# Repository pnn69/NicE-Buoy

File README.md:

# NicE-Buoy Autonomous Marine System Firmware

Welcome to the master repository for the **NicE-Buoy Autonomous Marine System**. This codebase powers a highly reliable, dual-processor autonomous marine buoy designed for GPS lock-to-position, remote configuration, automated sailing, and live telemetry tracking over LoRa and WiFi (UDP).

---

## 📌 Project Overview

NicE-Buoy is an industrial-grade marine robotic system consisting of multiple hardware and software components. Each buoy uses a **dual-ESP32 architecture** split into a **Top Unit (RoboTop)** and a **Sub Unit (RoboSub)**, connected by a single-wire half-duplex serial link. This physical decoupling isolates high-frequency navigation, radio communication, and web server tasks (Top) from raw thruster driving, compass polling, and the PID motor loops (Sub).

Alongside the buoys sit two shore-side controllers: **RoboCYD**, a touchscreen unit that doubles as the field WiFi access point, and **RoboLora**, a USB/WiFi LoRa gateway.

---

## 🏗️ System Architecture

```
        ┌───────────────────────────┐        ┌───────────────────────────────┐
        │  RoboPythonDisplay (PC)   │        │  RoboCYD (touchscreen)        │
        │  Tkinter dashboard        │        │  - IS the field AP Robo_WiFi  │
        └────────────┬──────────────┘        │  - LoRa RX task + web UI      │
                     │ UDP / LoRa            └───────────────┬───────────────┘
                     │                                       │
        ┌────────────▼──────────────┐                        │
        │  RoboLora (gateway)       │   UDP 1001 (protocol)  │
        │  USB + WiFi <-> LoRa      │   UDP 1002 (debug log) │
        └────────────┬──────────────┘                        │
                     └───────────────┬───────────────────────┘
                                     │  LoRa 868 MHz  +  WiFi/UDP
┌────────────────────────────────────▼────────────────────────────────────────┐
│                                  RoboTop                                    │
│  - GPS polling (TinyGPS++, 0,0 placeholder rejected)                        │
│  - LoraTask: RF telemetry, ACK retry table (10 slots)                       │
│  - WiFiTask: web dashboard, UDP broadcast, OTA, captive portal, mDNS        │
│  - SercomTask: bridge to the Sub          - Button, buzzer, RGB LEDs        │
└────────────────────────────────────┬────────────────────────────────────────┘
                                     │  single-wire half-duplex UART
                                     │  Top TX 22 / RX 21  <->  Sub RX 5 / TX 18
┌────────────────────────────────────▼────────────────────────────────────────┐
│                                  RoboSub                                    │
│  - Dual ESC thrusters (BB & SB)     - ICM-20948 9-DoF compass + fusion      │
│  - Rudder & speed PID loops         - Owns ALL tuning in NVS                │
│  - Its own web dashboard (24 endpoints) and OTA                            │
└─────────────────────────────────────────────────────────────────────────────┘
```

The codebase is structured into the following decoupled sub-projects:

1.  **`RoboTop` (Top Unit)** — ESP32, FreeRTOS. Acquires GPS, hosts the HTML5 control dashboard, broadcasts telemetry over UDP and LoRa, and delegates motor execution to the Sub.
    Tasks: `GpsTask`, `LoraTask`, `WiFiTask`, `SerialTask` (SercomTask), `buttonTask`, `LedTask`, `buzzTask`.
2.  **`RoboSub` (Sub Unit)** — ESP32, FreeRTOS. Drives the thrusters, reads the compass, runs the PID loops, and is the **authoritative owner of all tuning parameters** (see below).
    Tasks: `CompassTask`, `EscTask`, `SerialTask`, `WiFiTask`, `LedTask`, `buzzTask`. The rudder and speed PIDs live in `pidrudspeed.cpp`.
3.  **`RoboCYD` (Touchscreen Controller)** — ESP32 + 320x240 TFT with resistive touch. Displays the fleet, sends commands, and **raises the field access point `Robo_WiFi`** when no home network is present. Has a dedicated LoRa receive task and serves both a dashboard and a standalone fullscreen map.
4.  **`RoboDependency` (`RoboCompute` + `RoboTone` libraries)** — shared code linked by Top and Sub. Navigation maths (`RouteToPoint`), the unified `RoboStruct`, `formatFloat`, and the telemetry encoder/decoder (`rfCode` / `rfDeCode`).
5.  **`RoboLora` (LoRa Gateway)** — USB-and-WiFi to LoRa gateway with its own web UI. Relays operator commands to the buoys; stamps its outgoing frames with sender ID `0x99`.
6.  **`RoboPythonDisplay` (Python GUI Monitor)** — Tkinter desktop dashboard (`RoboControl.py`) for up to 3 buoys: windroses, thruster indicators, battery voltages, PID menus.
7.  **`RoboChargingStation`** — solar monitoring and charging dock firmware.

### Who owns what

Worth stating plainly, because it drives a lot of the design:

*   **The Sub owns the tuning.** PID gains, compass offset, `holdRad`, thruster inversion and swap all live in the Sub's NVS. The Top holds a RAM copy only, fetched via `SETUPDATA` when the serial link comes up, and shown on the dashboards until the Sub reports again.
*   **`compassOffset`, `revBB`, `revSB` and `swap_BB_SB` are hull-specific** — they describe the physical boat, not the electronics. Move a Sub to another hull and these travel with it and will be wrong until re-entered.
*   **The Sub has no LoRa.** Its only path to the outside world is the serial line to its Top.

---

## 🌐 Network Layout

Every node follows the same priority list:

```
NicE_WiFi  ->  Robo_WiFi  ->  its own AP
```

*   **At home** everything joins `NicE_WiFi`.
*   **In the field**, when no `NicE_WiFi` is in reach, the **CYD becomes `Robo_WiFi`** (password `geenanker`, `192.168.1.1/24`, 8 client slots) and the Tops and RoboLora join it.
*   **A node that finds neither** raises its own AP — `TOP_<id>`, `SUB_<id>`, `LORA_<id>`, password `geenanker`, on `192.168.4.1` — and keeps hunting underneath it. Joining that AP opens the dashboard automatically via a captive portal.
*   **The Sub deliberately skips `Robo_WiFi`**, to keep the CYD's client slots for the Tops and a phone. It costs nothing: the Sub never transmits on UDP anyway, and all of its telemetry reaches you folded into the Top's `TOPDATA`.

**mDNS** gives every node a stable name that works in both modes — `top-<id>.local`, `sub-<id>.local`, `robocyd.local`, `lora-<id>.local`. ArduinoOTA registers the responder; nothing else may call `MDNS.begin()`, as a second responder has crashed this hardware before.

**UDP ports:** `1001` carries the protocol; `1002` carries a plain-text debug log (see the RoboTop README).

---

## 📡 Communication Protocol & Frame Format

The system communicates using a lightweight, proprietary, ASCII-based comma-separated protocol designed to optimize RF bandwidth while remaining human-readable.

### Frame Anatomy
```
$TargetID,SenderID,AckType,CommandType,Status,Param1,Param2,...,ParamN*CRC\n
```

*   **`$`**: Starting sentinel character.
*   **`TargetID`**: Address of the recipient. **All IDs are hexadecimal.** A buoy's ID is the low four bytes of its MAC (e.g. `b7a5b578`). `1` (`BUOYIDALL`) is the broadcast address; `0` is treated as a legacy broadcast.
*   **`SenderID`**: Address of the transmitting station. `99` (i.e. `0x99`) is the web UI / RoboLora and `98` is the CYD display. **These two are the only senders whose broadcasts a buoy will act on** — a broadcast command from a peer buoy is ignored, which is what stops one buoy commanding another.
*   **`AckType`**: Packet type classification:
    *   `1 (GET)`: Request parameter values.
    *   `2 (SET)`: Modify parameter values.
    *   `3 (GETACK)`: Request command execution with receipt verification.
    *   `4 (ACK)`: Receipt confirmation.
    *   `6 (INF)`: Telemetry status update, or an *answer* to a question.
*   **`CommandType`**: Integer mapping to system command (e.g., `51` for `TOPDATA`, `19` for `BUOYPOS`, `83` for `SETUPDATA`, `47` for `DIRDIST`, `21` for `LOCKPOS`, `23` for `DOCKPOS`).
*   **`Status`**: Current state machine status of the buoy (`7 IDLE`, `13 LOCKED`, `16 DOCKED`, …).
*   **`Params`**: Dynamic floating-point or integer parameters depending on the command.
*   **`*`**: End-of-payload delimiter.
*   **`CRC`**: 2-character hexadecimal CRC calculated by XOR'ing all characters between `$` and `*`.

> **Broadcasts that expect an ACK are a trap.** An ACK for `IDr = BUOYIDALL` can never match in `removeAckMsg()`, so a `SET` or `GETACK` broadcast sits in the LoRa retry table for all five retransmits and blocks a slot. Broadcast beacons must use `INF`.

---

## 🚀 Advanced Telemetry Optimizations

### 1. Bandwidth Compression
To maximize LoRa airtime efficiency and range, telemetry strings undergo two compression steps in `RoboCompute.cpp`:
*   **Float Trailing Stripping**: `formatFloat()` trims redundant trailing zeros and decimal points (e.g. `12.5000` becomes `12.5`).
*   **Zero Compression**: `RoboCode()` compresses consecutive zero fields to empty strings (e.g. `,0,0,0,0,` becomes `,,,,,`).

### 2. The Top-to-Sub Link, and Why One-Way Failures Matter
The Top and Sub share **one wire**, half duplex, with hardware separating the two directions (opto-isolated; see `Datasheets/`). The firmware configures two GPIOs per board — Top TX 22 / RX 21, Sub RX 5 / TX 18 — but that is **not** two conductors.

*   **The diagnostic consequence:** if the connector or the wire fails, traffic stops in *both* directions. A failure in **one direction only** therefore cannot be the plug — it is in the direction-separation circuitry, which is per board. Swapping a Sub between hulls localises such a fault to a specific board.
*   `SercomTask` implements **echo filtering**, discarding frames whose sender ID is its own, because a transmitter hears itself on a shared wire.
*   **Implicit ACKs**: any valid `INF` response from the Sub signals that it processed the command, clearing the retry queue without extra traffic.
*   **The Sub sleeps.** After reconnection it sits in power-down and only wakes on an incoming command — send one, wait, then it communicates. Do not read a quiet Sub as a fault until it has been nudged.

### 3. Hardware Self-Healing Watchdogs
*   **LoRa transceiver watchdog**: if transmission fails for 500 ms the SPI/state machine is assumed locked and `InitLora()` forces a full re-init.
*   **Compass watchdog**: static I2C readings under thruster power trigger `COMPASS STUCK - REINIT`.
*   **Serial watchdog**: the Top clears `isSerConnected` after 2 s of silence and re-requests `SETUPDATA` when the Sub returns.
*   **Stack headroom is observable.** The Top's `/data` reports `StkLoop`, `StkLora`, `StkWifi`, `StkSer` and heap figures. A LoRa task running on 100 bytes of stack was the cause of a hard-to-find panic; check these after any change that adds work to a task.

---

## 🧭 In-Field Navigation Calibration State Machines

1.  **In-Field Compass Spin Calibration** — self-guided rotation while measuring magnetic min/max to derive hard-iron offsets.
2.  **In-Field Offset Alignment** — sails a straight leg on compass heading, compares the GPS track, and writes the difference to the stored compass offset.
3.  **Guided 8-Point Compass Calibration** — the hull is turned to the compass's own zero and then indexed round a mechanical fixture 45° at a time, one capture per mark. Produces the 8-point correction table, which is held on the Sub and reported through `SETUPDATA`. The table describes the hull's magnetic deviation only; which way the sensor is bolted in is a separate setting (**Set as North**), applied after the table.

    A GPS-based version of this used to exist, sailing eight 100 m legs and inferring the table from the track. It was removed when the mounting offset moved out of the table's input — its residual arithmetic assumed the old ordering.

---

## 🛠️ Developer Guide

### Prerequisites
*   **Firmware**: [VS Code](https://code.visualstudio.com/) + [PlatformIO IDE](https://platformio.org/).
*   **Python Monitor**: Python 3.10+ with `pyserial` and `tkinter`.

### Compilation & Flash Commands
```bash
pio run                      # build
pio run -t upload            # upload (OTA by default for Top and Sub)
pio device monitor           # serial monitor
```

### Over-The-Air (OTA) Updates
`RoboTop` and `RoboSub` default to `upload_protocol = espota`, so a plain upload goes over the network:

```bash
pio run -t upload --upload-port 192.168.1.71        # by address
pio run -t upload --upload-port top-b7a5099c.local  # or by mDNS name
```

`RoboCYD` and `RoboLora` have **no espota configuration** in their `platformio.ini` (their `upload_port` names a COM port that may not exist), so flash those directly:

```bash
python ~/.platformio/packages/framework-arduinoespressif32/tools/espota.py \
       -i <ip> -p 3232 -f .pio/build/<env>/firmware.bin -r
```

A RoboTop change that touches `data/` also needs `pio run -t uploadfs` — the web page lives in SPIFFS.

> Renaming an SSID or changing the WiFi policy must be rolled out to **the whole fleet at home on `NicE_WiFi`**. A device left on the old scheme cannot be reached in the field.

### Running the Python GUI Dashboard
```bash
pip install pyserial
python RoboPythonDisplay/RoboControl.py
```

---

## 📜 License & Contributions
This project is proprietary and confidential. For contributions, pull requests, or feature requests, contact **Peter de Nijs** (`pnn69pnn@gmail.com`).

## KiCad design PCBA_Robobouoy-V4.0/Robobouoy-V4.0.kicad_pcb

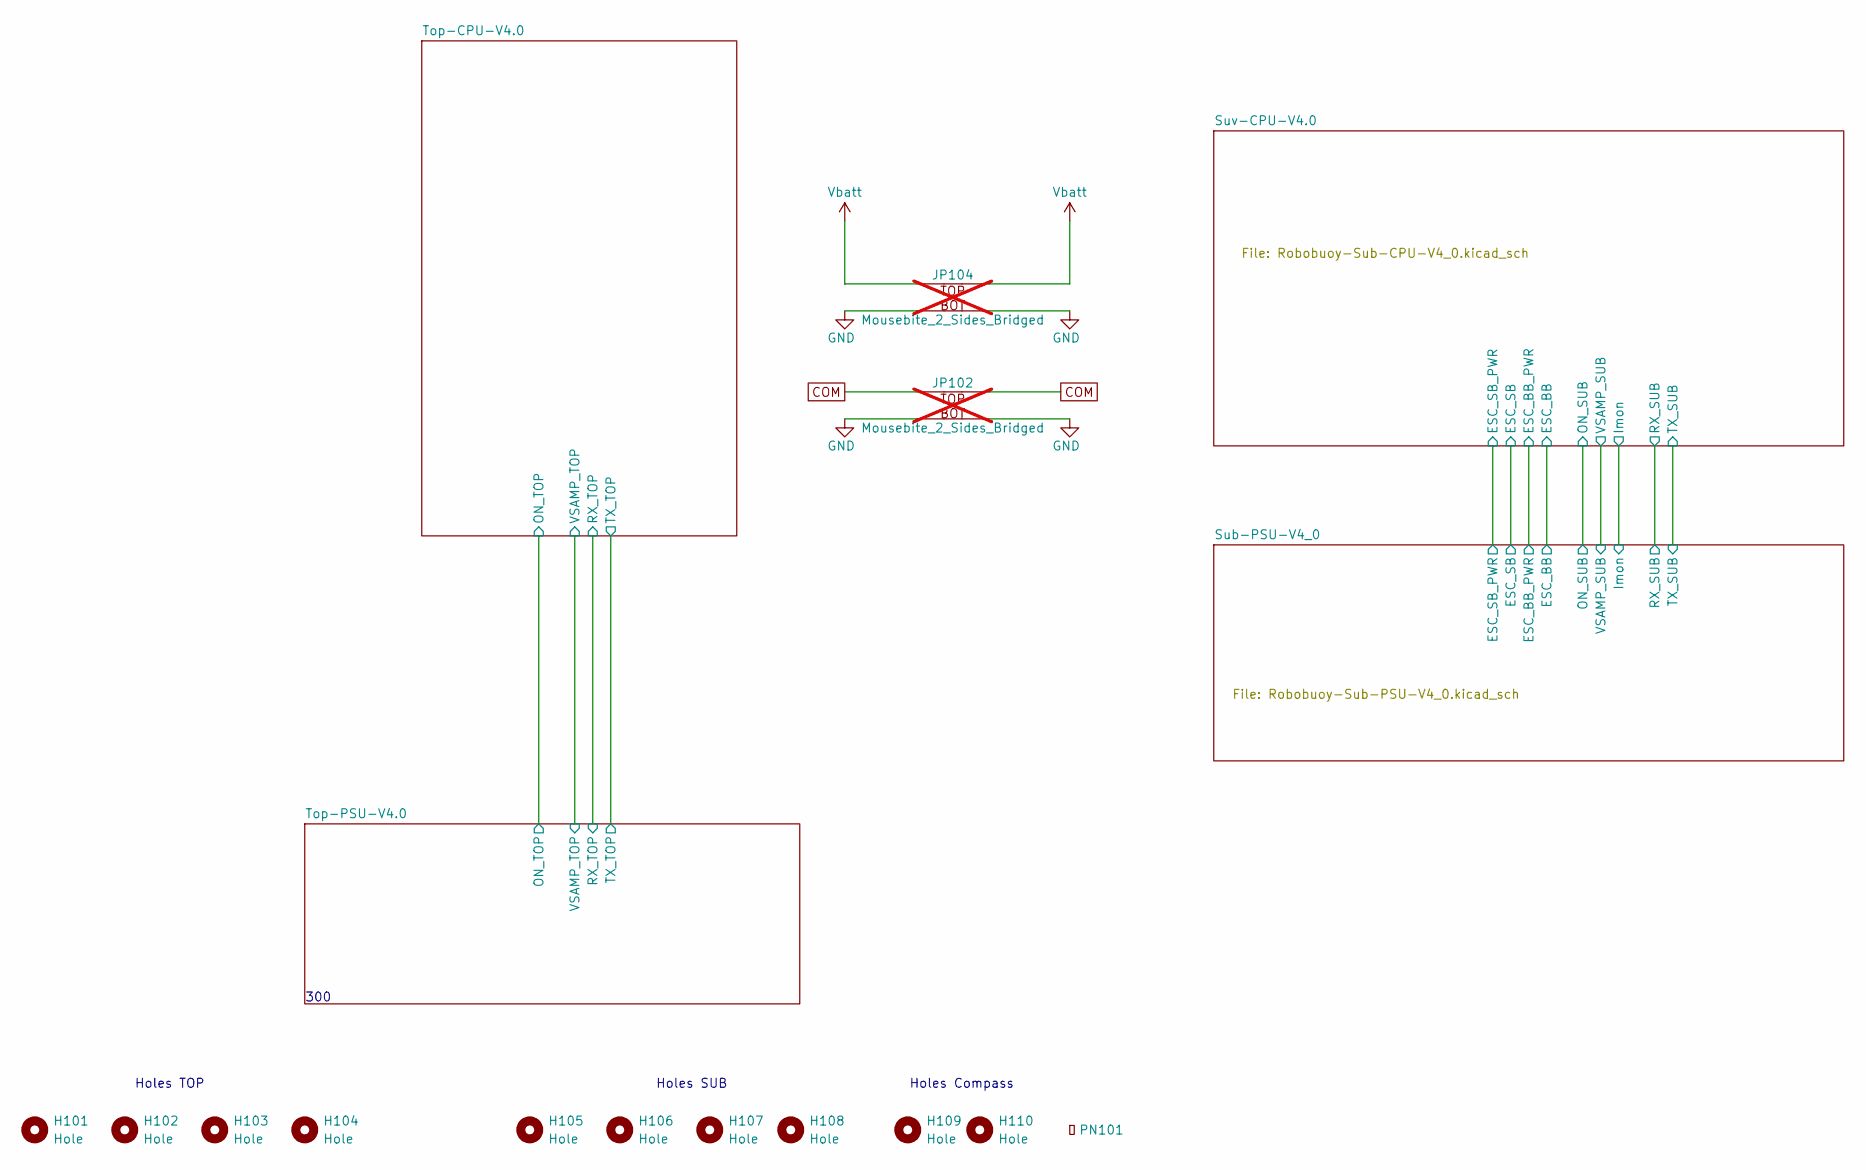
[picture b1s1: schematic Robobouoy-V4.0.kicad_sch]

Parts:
H101, H102, H103, H104, H105, H106, H107, H108, H109, H110: Hole; Hole_3.1mm
JP102, JP104: Mousebite_2_Sides_Bridged; MousebitConnectorDoubleSided; not fitted
PN101: Part_Num_JLCPCB

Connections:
COM: JP102.1 (A), JP102.2 (B); also elsewhere on the board
GND: JP102.3 (C), JP102.4 (D), JP104.3 (C), JP104.4 (D); also elsewhere on the board
Vbatt: JP104.1 (A), JP104.2 (B); also elsewhere on the board

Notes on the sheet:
Holes TOP
300
Holes SUB
Holes Compass

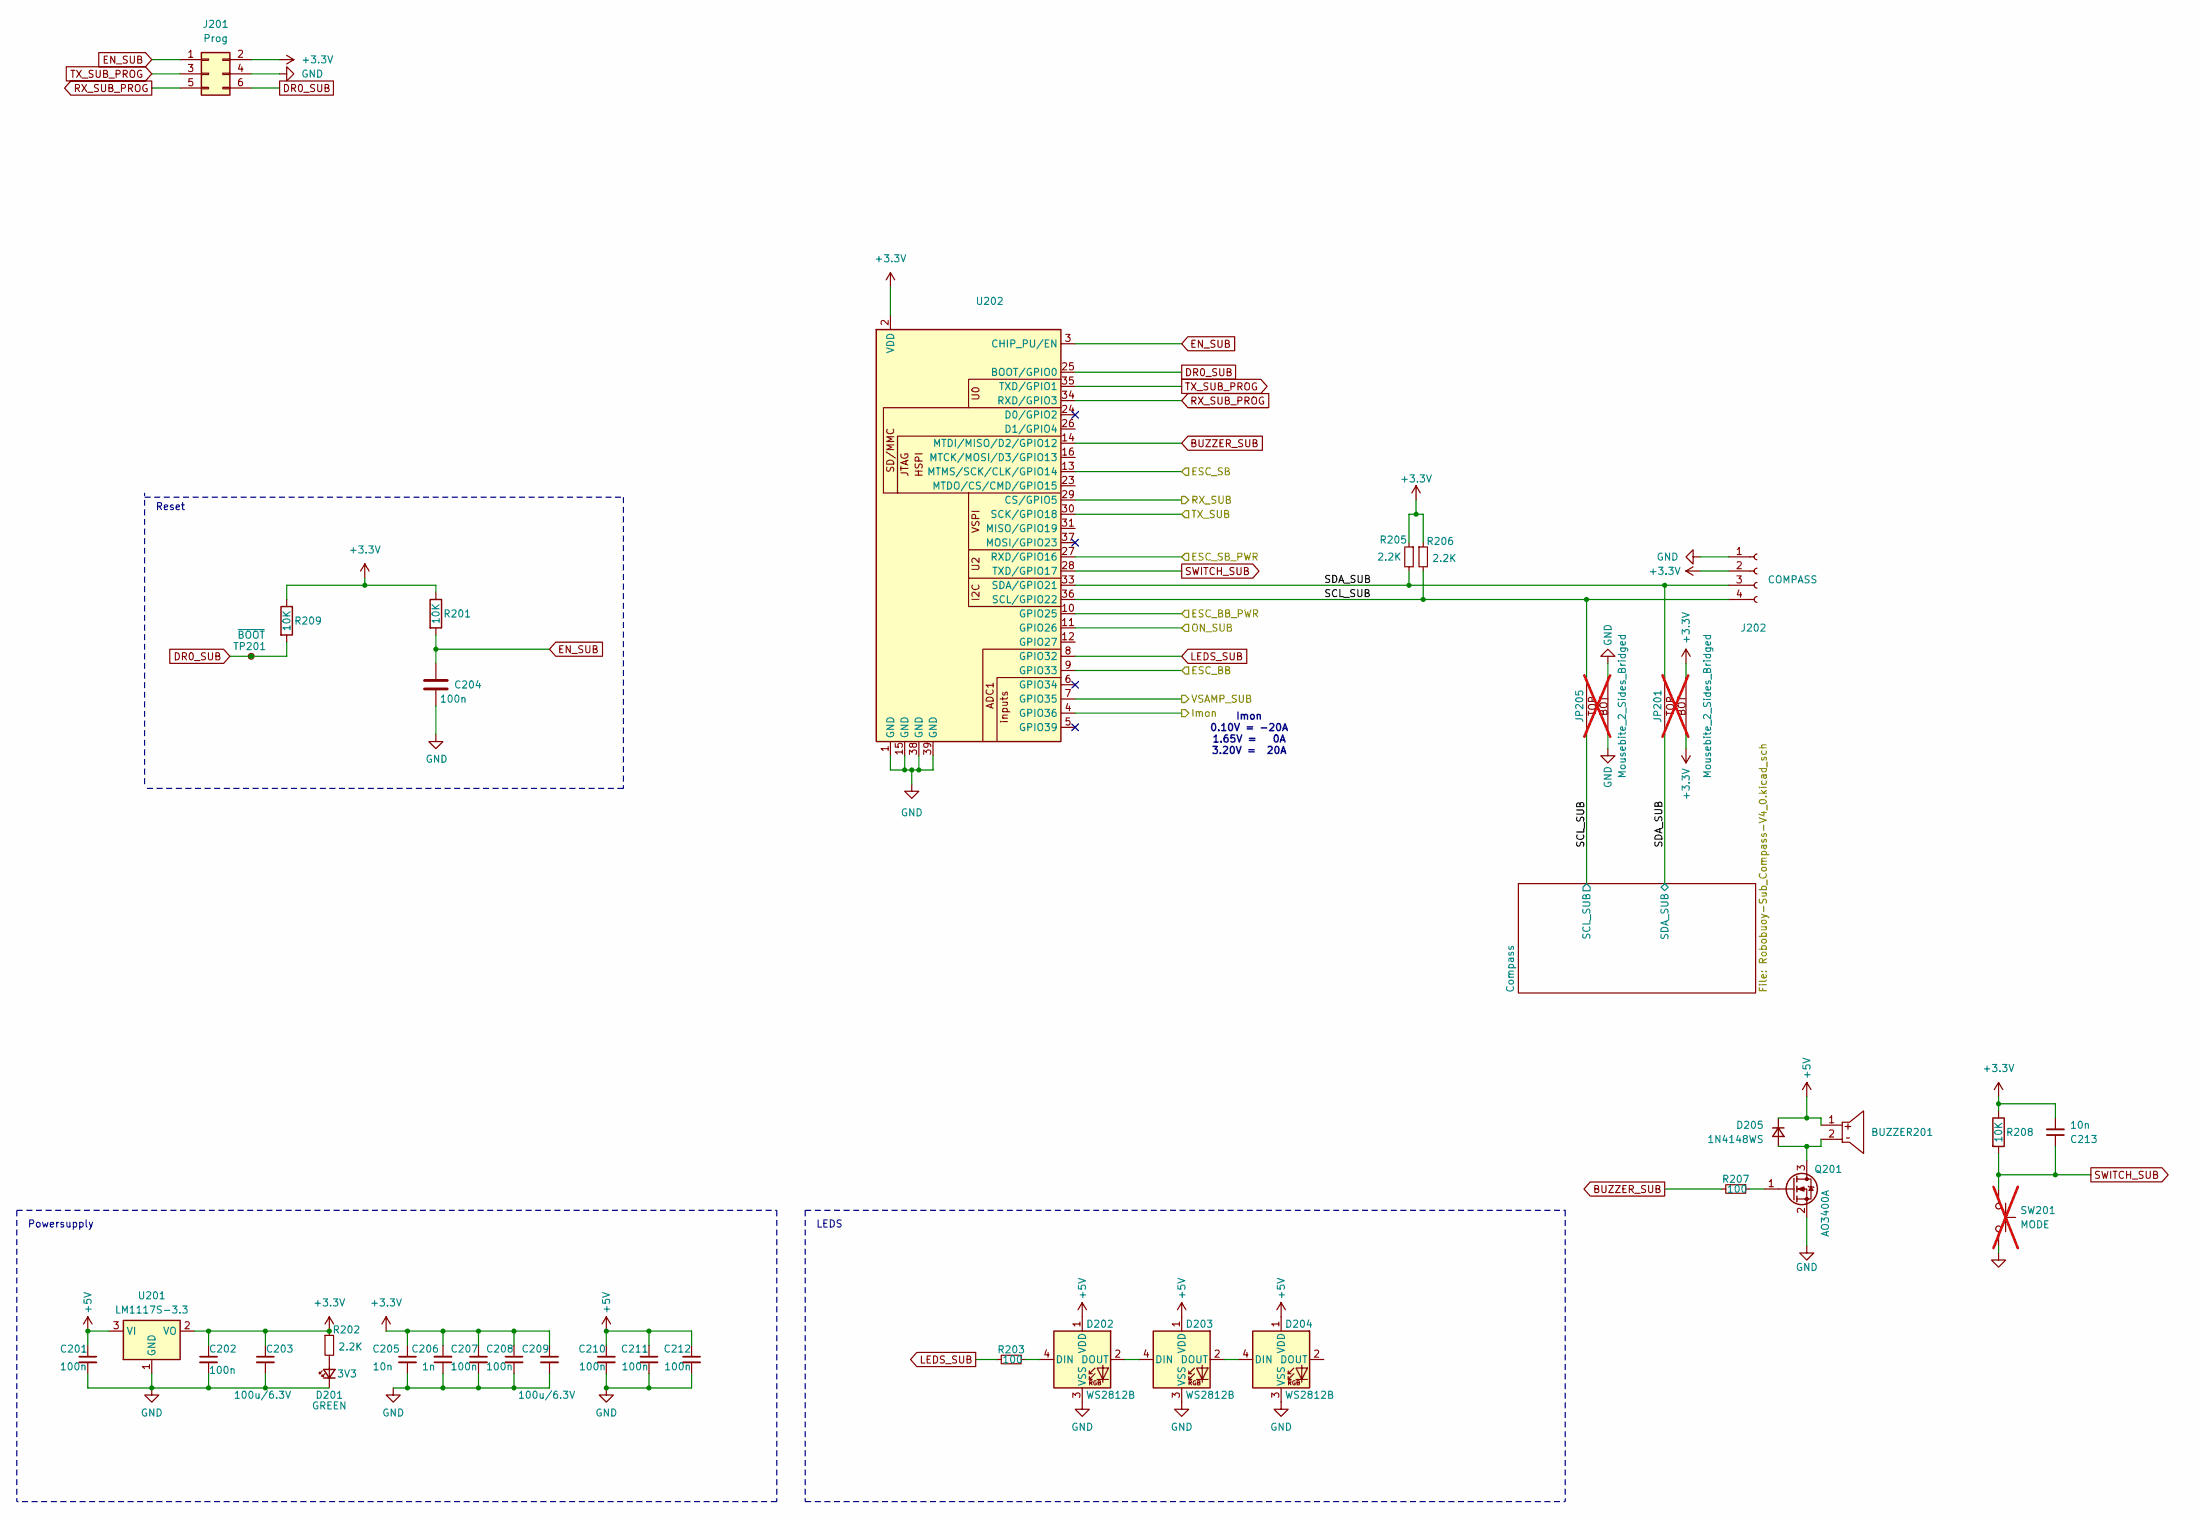
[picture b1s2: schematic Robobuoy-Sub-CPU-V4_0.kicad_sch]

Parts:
BUZZER201: CY-12085G-3016-P4; BUZ-TH_BD12.0-P6.50-D0.6-FD; MPN Cy-12085G-3016-P4; LCSC Part C968749
C201, C202, C204, C207, C208, C210, C211, C212: 100n; C_0603; LCSC C14663
C203, C209: 100u/6.3V; C_1206_3216Metric; LCSC C16133
C205, C213: 10n; C_0603; LCSC C57112
C206: 1n; C_0603; LCSC C1588
D201: GREEN; LED_0603_1608Metric; LCSC C12624
D202, D203, D204: WS2812B; LED_WS2812B_PLCC4_5.0x5.0mm_P3.2mm; LCSC C2843785
D205: 1N4148WS; D_SOD-323_1.8x1.4x1.15; LCSC C2128
J201: Prog; IDC_2x3_1.27mm; LCSC C42372545
J202: COMPASS; JST_XH_B4B-XH-A_1x04_P2.50mm_Vertical; LCSC C5341203
JP201, JP205: Mousebite_2_Sides_Bridged; MousebitConnectorDoubleSided; not fitted
Q201: AO3400A; SOT-23; LCSC C20917
R201, R208, R209: 10K; R_0603; Farnell 2331736
R202, R205, R206: 2.2K; R_0603; LCSC C4190
R203, R207: 100; R_0603; LCSC C22775
SW201: MODE; Header_1x02_P2.54_Jumper; not fitted
TP201: ~{BOOT}; Testpad_1
U201: LM1117S-3.3; SOT223; LCSC C6186
U202: ESP32-WROOM-32E_(visible_peripherals); ESP32-WROOM-32; LCSC C82899

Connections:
+3.3V: C202.1, C203.1, C205.1, C206.2, C207.1, C208.1, C209.1, C213.2, J201.2, J202.2, JP201.3 (C), JP201.4 (D), R201.1, R202.1, R205.1, R206.1, R208.1, R209.1, U201.2 (VO), U202.2 (VDD); also elsewhere on the board
+5V: BUZZER201.1, C201.1, C210.1, C211.1, C212.1, D202.1 (VDD), D203.1 (VDD), D204.1 (VDD), D205.1 (K), U201.3 (VI); also elsewhere on the board
/Sub-PSU-V4_0/ESC_BB: U202.9 (GPIO33); also elsewhere on the board
/Sub-PSU-V4_0/ESC_BB_PWR: U202.10 (GPIO25); also elsewhere on the board
/Sub-PSU-V4_0/ESC_SB: U202.13 (MTMS/SCK/CLK/GPIO14); also elsewhere on the board
/Sub-PSU-V4_0/ESC_SB_PWR: U202.27 (RXD/GPIO16); also elsewhere on the board
/Sub-PSU-V4_0/Imon: U202.4 (GPIO36); also elsewhere on the board
/Sub-PSU-V4_0/ON_SUB: U202.11 (GPIO26); also elsewhere on the board
/Sub-PSU-V4_0/RX_SUB: U202.29 (CS/GPIO5); also elsewhere on the board
/Sub-PSU-V4_0/TX_SUB: U202.30 (SCK/GPIO18); also elsewhere on the board
/Sub-PSU-V4_0/VSAMP_SUB: U202.7 (GPIO35); also elsewhere on the board
/Suv-CPU-V4.0/SCL_SUB: J202.4, JP205.1 (A), JP205.2 (B), R206.2, U202.36 (SCL/GPIO22); also elsewhere on the board
/Suv-CPU-V4.0/SDA_SUB: J202.3, JP201.1 (A), JP201.2 (B), R205.2, U202.33 (SDA/GPIO21); also elsewhere on the board
BUZZER_SUB: R207.2, U202.14 (MTDI/MISO/D2/GPIO12)
DR0_SUB: J201.6, R209.2, TP201.1 (1_1), U202.25 (BOOT/GPIO0)
EN_SUB: C204.1, J201.1, R201.2, U202.3 (CHIP_PU/EN)
GND: C201.2, C202.2, C203.2, C204.2, C205.2, C206.1, C207.2, C208.2, C209.2, C210.2, C211.2, C212.2, D201.1 (K), D202.3 (VSS), D203.3 (VSS), D204.3 (VSS), J201.4, J202.1, JP205.3 (C), JP205.4 (D), Q201.2 (S), SW201.1, U201.1 (GND), U202.1 (GND), U202.15 (GND), U202.38 (GND), U202.39 (GND); also elsewhere on the board
LEDS_SUB: R203.2, U202.8 (GPIO32)
unnamed: D201.2 (A), R202.2
unnamed: D202.4 (DIN), R203.1
unnamed: D202.2 (DOUT), D203.4 (DIN)
unnamed: D203.2 (DOUT), D204.4 (DIN)
unnamed: BUZZER201.2, D205.2 (A), Q201.3 (D)
unnamed: Q201.1 (G), R207.1
RX_SUB_PROG: J201.5, U202.34 (RXD/GPIO3)
SWITCH_SUB: C213.1, R208.2, SW201.2, U202.28 (TXD/GPIO17)
TX_SUB_PROG: J201.3, U202.35 (TXD/GPIO1)

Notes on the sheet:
LEDS
Imon 0.10V = -20A 1.65V = 0A 3.20V = 20A
Powersupply
Reset

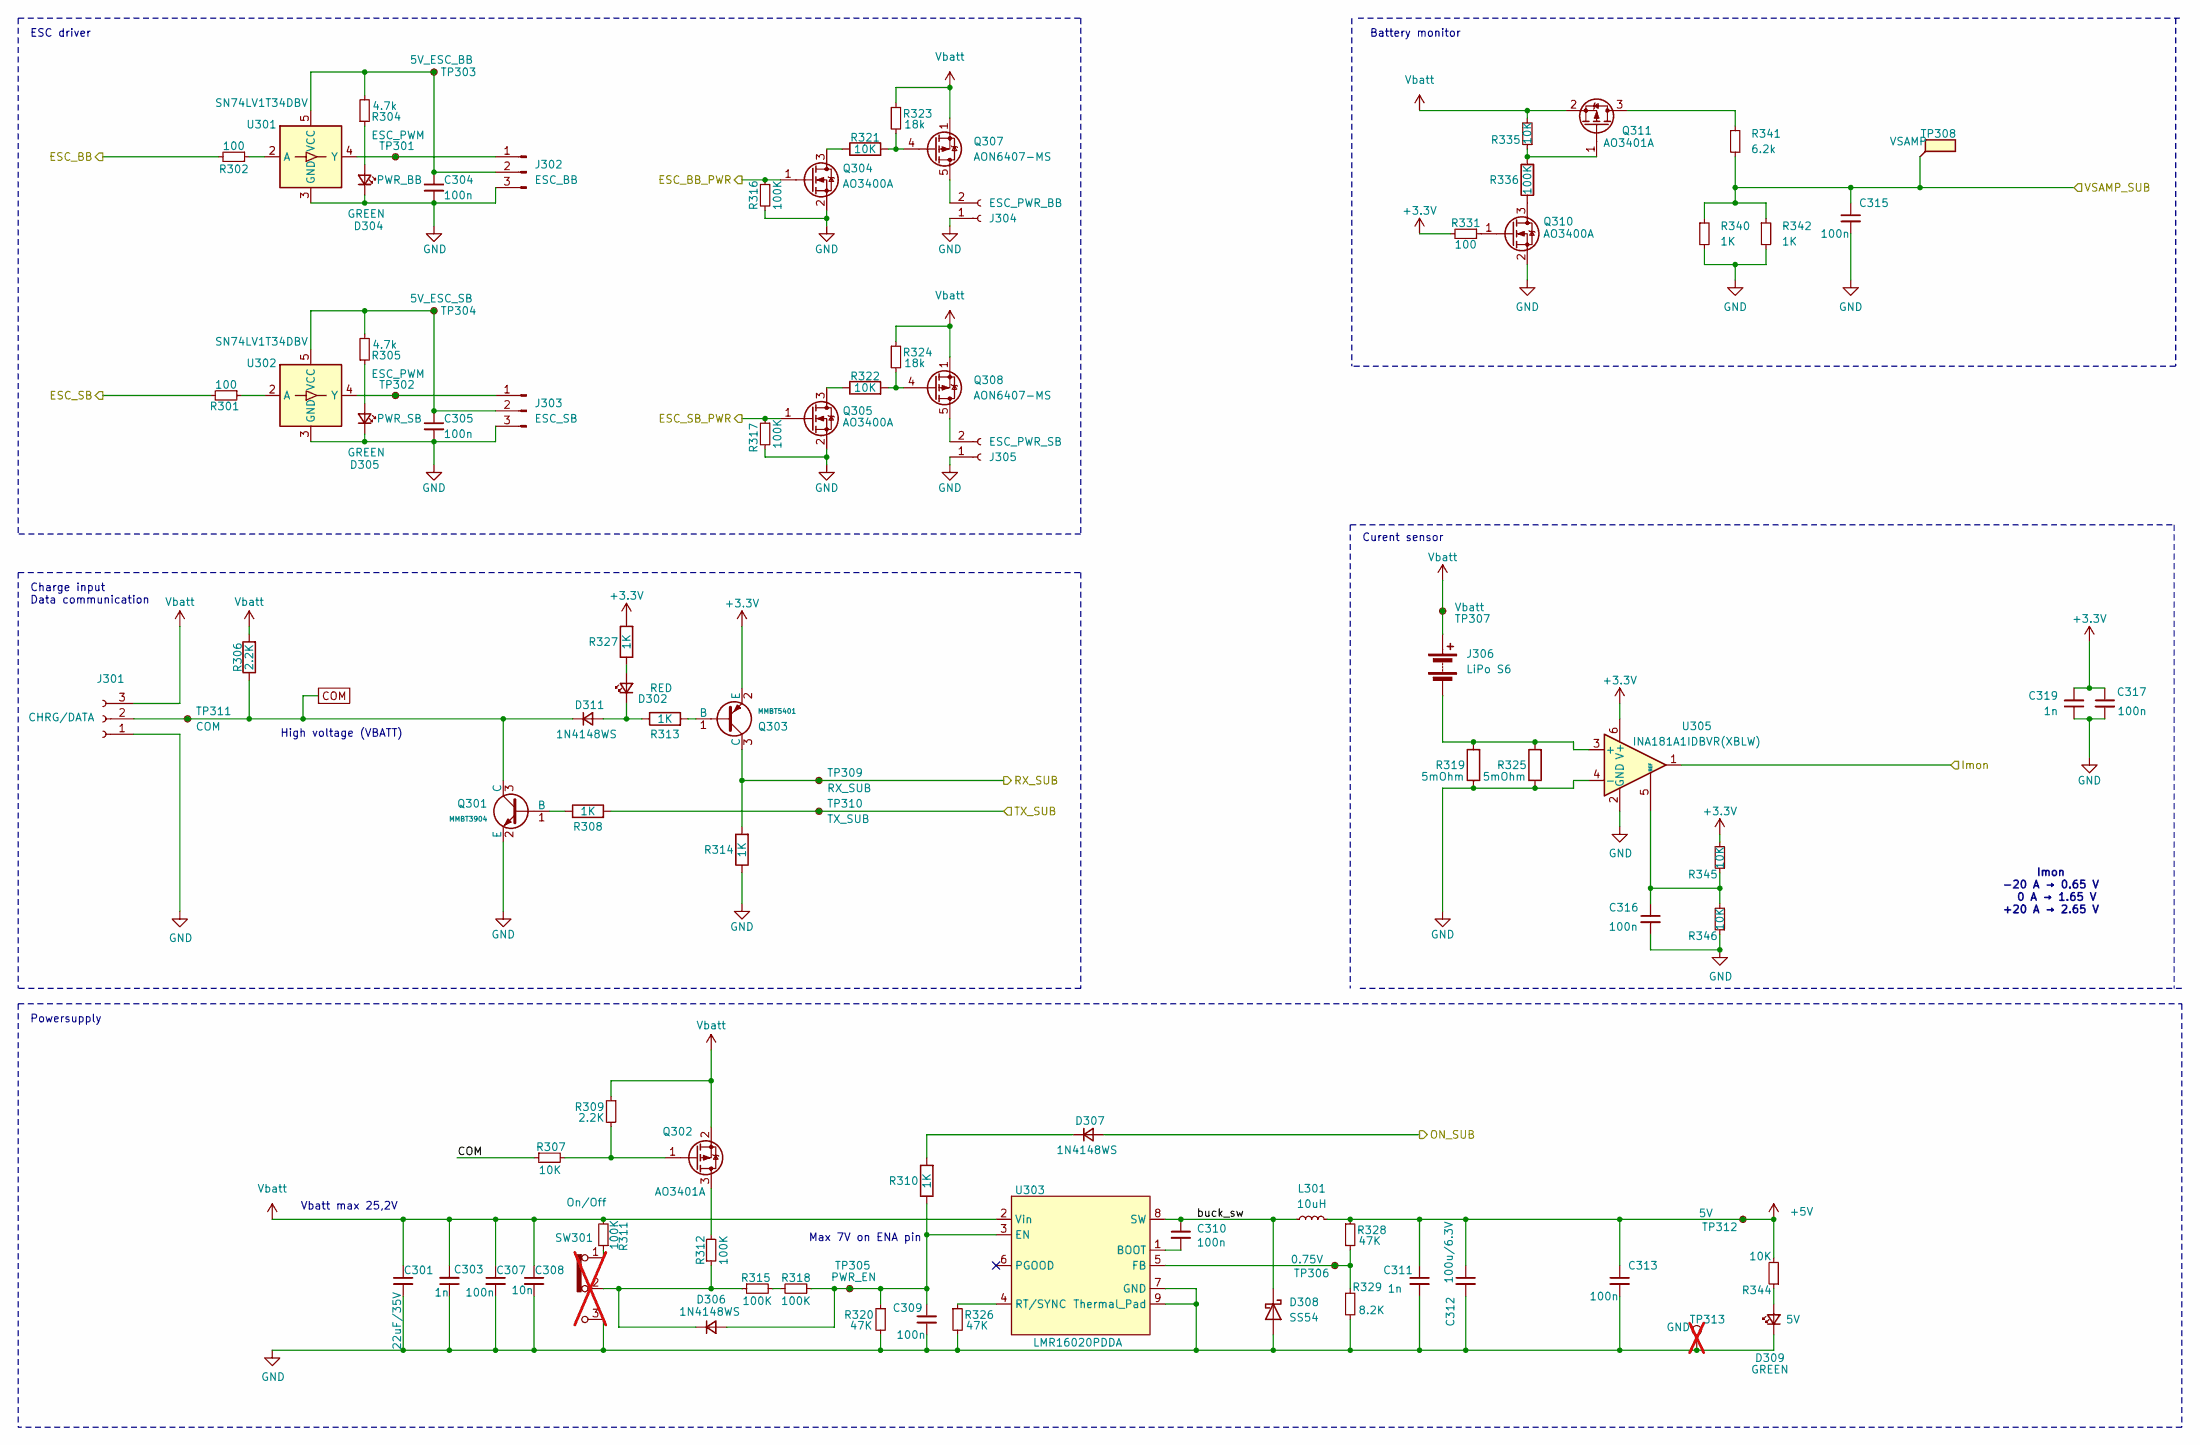
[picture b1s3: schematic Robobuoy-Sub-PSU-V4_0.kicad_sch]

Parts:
C301: 22uF/35V; C_1206_3216Metric; LCSC C6119969
C303, C311, C319: 1n; C_0603; LCSC C1588
C304, C305, C307, C309, C310, C313, C315, C316, C317: 100n; C_0603; LCSC C14663
C308: 10n; C_0603; LCSC C57112
C312: 100u/6.3V; C_1206_3216Metric; LCSC C16133
D302: RED; LED_0603_1608Metric; LCSC C2286
D304, D305, D309: GREEN; LED_0603_1608Metric; LCSC C2286
D306, D307, D311: 1N4148WS; D_SOD-323_1.8x1.4x1.15; LCSC C2128
D308: SS54; D_SMA; LCSC C22452
J301: CHRG/DATA; MR60PB-M; LCSC C53087234
J302: ESC_BB; JST_XH_B3B-XH-A_1x03_P2.50mm_Vertical; LCSC C5341202
J303: ESC_SB; JST_XH_B3B-XH-A_1x03_P2.50mm_Vertical; LCSC C5341202
J304: ESC_PWR_BB; AMASS_XT60PB-F_1x02_P7.20mm_Vertical; LCSC C19268038
J305: ESC_PWR_SB; AMASS_XT60PB-F_1x02_P7.20mm_Vertical; LCSC C19268038
J306: LiPo S6; AMASS_XT60PB-M_1x02_P7.20mm_Vertical; LCSC C19268037
L301: 10uH; L_6.6x7.0mm; LCSC C2894722
Q301: MMBT3904; Q_SOT-23; Part MMBT3904; LCSC C7420353
Q302, Q311: AO3401A; SOT-23; LCSC C15127
Q303: MMBT5401; Q_SOT-23; Part MMBT5401; LCSC C7420356
Q304, Q305, Q310: AO3400A; SOT-23; LCSC C20917
Q307, Q308: AON6407-MS; AO_DFN-8-1EP_5.55x5.2mm_P1.27mm_EP4.12x4.6mm; LCSC C17702953
R301, R302, R331: 100; R_0603; LCSC C22775
R304, R305: 4.7k; R_0603; LCSC C4177
R306, R309: 2.2K; R_0603; LCSC C4190
R307, R321, R322, R335, R344, R345, R346: 10K; R_0603; LCSC C25804
R308, R310, R313, R314, R327, R340, R342: 1K; R_0603; LCSC C21190
R311, R312, R315, R316, R317, R318, R336: 100K; R_0603; LCSC C25803
R319, R325: 5mOhm; R_1206; LCSC C7419996
R320, R326, R328: 47K; R_0603; LCSC C25819
R323, R324: 18k; R_0603; LCSC C25810
R329: 8.2K; R_0603; LCSC C25981
R341: 6.2k; R_0603; LCSC C4260
SW301: On/Off; Header_1x03_P2.54_Male; LCSC C2937625; not fitted
TP301, TP302: ESC_PWM; Testpad_1
TP303: 5V_ESC_BB; Testpad_1
TP304: 5V_ESC_SB; Testpad_1
TP305: PWR_EN; Testpad_1
TP306: 0.75V; Testpad_1
TP307: Vbatt; Testpad_1
TP308: VSAMP; Testpad_1
TP309: RX_SUB; Testpad_1
TP310: TX_SUB; Testpad_1
TP311: COM; Testpad_1
TP312: 5V; Testpad_1
TP313: GND; Testpoint_0.9x1.5; not fitted
U301, U302: SN74LV1T34DBV; SOT-23-5; LCSC C100024
U303: LMR16020PDDA; SOIC-8-1EP_3.9x4.9mm_P1.27mm_EP2.41x3.81mm_ThermalVias; LCSC C190006
U305: INA181A1IDBVR(XBLW); SOT-23-6; LCSC C45351496

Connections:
+3.3V: C317.1, C319.2, Q303.2 (E), R327.2, R331.2, R345.2, U305.6 (V+); also elsewhere on the board
+5V: C311.1, C312.1, C313.1, L301.2, R328.1, R344.2, TP312.1 (1_1); also elsewhere on the board
/Sub-PSU-V4_0/ESC_BB: R302.2; also elsewhere on the board
/Sub-PSU-V4_0/ESC_BB_PWR: Q304.1 (G), R316.1; also elsewhere on the board
/Sub-PSU-V4_0/ESC_SB: R301.2; also elsewhere on the board
/Sub-PSU-V4_0/ESC_SB_PWR: Q305.1 (G), R317.1; also elsewhere on the board
/Sub-PSU-V4_0/Imon: U305.1; also elsewhere on the board
/Sub-PSU-V4_0/ON_SUB: D307.2 (A); also elsewhere on the board
/Sub-PSU-V4_0/RX_SUB: Q303.3 (C), R314.2, TP309.1 (1_1); also elsewhere on the board
/Sub-PSU-V4_0/TX_SUB: R308.2, TP310.1 (1_1); also elsewhere on the board
/Sub-PSU-V4_0/VSAMP_SUB: C315.1, R340.1, R341.2, R342.1, TP308.1 (1_1); also elsewhere on the board
/Sub-PSU-V4_0/buck_sw: C310.1, D308.1 (K), L301.1, U303.8 (SW)
COM: D311.1 (K), J301.2, Q301.3 (C), R306.1, R307.1, TP311.1 (1_1); also elsewhere on the board
GND: C301.2, C303.1, C304.2, C305.2, C307.2, C308.2, C309.2, C311.2, C312.2, C313.2, C315.2, C316.2, C317.2, C319.1, D304.1 (K), D305.1 (K), D308.2 (A), D309.1 (K), J301.1, J302.3, J303.3, J304.1, J305.1, Q301.2 (E), Q304.2 (S), Q305.2 (S), Q310.2 (S), R314.1, R316.2, R317.2, R319.1, R320.2, R325.1, R326.2, R329.2, R340.2, R342.2, R346.1, SW301.3, TP313.1 (1_1), U301.3 (GND), U302.3 (GND), U303.7 (GND), U303.9 (Thermal_Pad), U305.2 (GND), U305.4 (-); also elsewhere on the board
unnamed: D302.2 (A), R327.1
unnamed: D302.1 (K), D311.2 (A), R313.1
unnamed: D304.2 (A), R304.1
unnamed: D305.2 (A), R305.1
unnamed: C309.1, D306.2 (A), R310.1, R318.1, R320.1, TP305.1 (1_1), U303.3 (EN)
unnamed: D306.1 (K), R312.1, R315.1, SW301.2
unnamed: D307.1 (K), R310.2
unnamed: D309.2 (A), R344.1
unnamed: J302.1, TP301.1 (1_1), U301.4 (Y)
unnamed: C304.1, J302.2, R304.2, TP303.1 (1_1), U301.5 (VCC)
unnamed: J303.1, TP302.1 (1_1), U302.4 (Y)
unnamed: C305.1, J303.2, R305.2, TP304.1 (1_1), U302.5 (VCC)
unnamed: J304.2, Q307.5 (D)
unnamed: J305.2, Q308.5 (D)
unnamed: J306.1 (-), R319.2, R325.2, U305.3 (+)
unnamed: Q301.1 (B), R308.1
unnamed: Q302.3 (D), R312.2
unnamed: Q302.1 (G), R307.2, R309.2
unnamed: Q303.1 (B), R313.2
unnamed: Q304.3 (D), R321.1
unnamed: Q305.3 (D), R322.1
unnamed: Q307.4 (G), R321.2, R323.2
unnamed: Q308.4 (G), R322.2, R324.2
unnamed: Q310.3 (D), R336.1
unnamed: Q310.1 (G), R331.1
unnamed: Q311.3 (D), R341.1
unnamed: Q311.1 (G), R335.1, R336.2
unnamed: R311.1, SW301.1
unnamed: R315.2, R318.2
unnamed: R302.1, U301.2 (A)
unnamed: R301.1, U302.2 (A)
unnamed: C310.2, U303.1 (BOOT)
unnamed: R328.2, R329.1, TP306.1 (1_1), U303.5 (FB)
unnamed: R326.1, U303.4 (RT/SYNC)
unnamed: C316.1, R345.1, R346.2, U305.5 (REF)
Vbatt: C301.1, C303.2, C307.1, C308.1, J301.3, J306.2 (+), Q302.2 (S), Q307.1 (S), Q307.2 (S), Q307.3 (S), Q308.1 (S), Q308.2 (S), Q308.3 (S), Q311.2 (S), R306.2, R309.1, R311.2, R323.1, R324.1, R335.2, TP307.1 (1_1), U303.2 (Vin); also elsewhere on the board

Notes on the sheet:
Max 7V on ENA pin
Vbatt max 25,2V
ESC driver
Curent sensor
Powersupply
Charge input Data communication
Battery monitor
High voltage (VBATT)
Imon -20 A → 0.65 V 0 A → 1.65 V +20 A → 2.65 V

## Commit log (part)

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2026-04-19 feat: implement on-device 3D Ellipsoid Fit for soft iron calibration
    - Integrated a self-contained 9-parameter Least Squares Ellipsoid Fit algorithm (MagCalibrator) to replace legacy hard-iron-only min/max calibration.
    - Added support for 3x3 soft iron transformation matrices for both LSM303 and ICM20948 sensors.
    - Updated CalibrateCompass() to collect 3D magnetic point clouds and solve for both hard iron offsets and soft iron scaling/rotation in the field.
    - Implemented automatic fallback to min/max Hard Iron calibration if the ellipsoid fit fails due to insufficient data geometry.
    - Refactored heading calculation to apply the full matrix transformation: Corrected = SoftIronMatrix * (Raw -
2026-04-19 feat: distinct happy/sad audio feedback for compass calibration on both Sub and Top
    - Updated CalibrateCompass() on the Sub to evaluate the success of the 3D Ellipsoid Fit algorithm.
    - Added a happy beep (tune 5) upon successful fit, and a sad beep (tune 3) on fallback to Min/Max.
    - The Sub now temporarily updates its telemetry status to ERROR on failure, allowing the Top unit to read the outcome.
    - (Manual Update) Modified RoboTop's buttonLight function to play beep(3) if sta->status is ERROR, and beep(5) otherwise when completing calibration.
2026-04-19 feat: complete ESC refactor, current sensing, and UI telemetry sync
    Sub Buoy (ESC & Power):
    - Swapped raw ledc for ESP32Servo library to resolve PWM timing/timer conflicts.
    - Forced ESC power pins HIGH in setup() for immediate module activation.
    - Implemented a reliable 3-second neutral arming sequence (1500us) for ESC initialization.
    - Added 60s initial grace period and Detach logic to preserve hardware timers during sleep.
    Sub Buoy (PID & ADC):
2026-04-21 Restore LSM compass heading logic and remove float vector typing bug
2026-05-16 Last dual compas mode
2026-05-16 feat: complete removal of dual compass system to single unified compass
2026-05-17 compass ok
2026-05-18 WIP: Fix Python offset and Top serial ID forwarding
2026-05-22 Update RoboTop and PCB project files
    - Sync RoboTop WiFi and Serial communication logic
    - Update RoboTop web interface data management
    - Update PlatformIO configuration for RoboTop
    - Update KiCad project settings and metadata for Sub v3.0 PCB
2026-05-24 Restore stable morning baseline and fix sensor data integrity
    - Reverted compass and subwifi to morning baseline to restore basic functionality
    - Refactored compass data pipeline to use float (4-byte) instead of double (8-byte) consistently
    - Fixed critical memory corruption bug in compass queue (double vs float size mismatch)
    - Optimized calibration data collection rate (reduced spatial filter threshold and added DRDY check)
    - Repositioned Windrose in web interface for better usability
    - Corrected heading rotation direction to track Sub physical movement
2026-05-30 Hybrid Compass V11.1 - Stabilization with vertical offset correction
    - Apply precise vertical Hard-Iron offset (-43.0) for LSM303AGR Mag
    - Stabilize tilt compensation by aligning Mag and Accel frames
    - Add raw XYZ and stored offset display to mobile dashboard
    - Finalize smoothing and North alignment for current hardware configuration
2026-05-31 V13.6 Supplement: Include missing header files and RoboTop communication updates.
2026-05-31 sub okay
2026-05-31 feat: Enhanced Telemetry Dashboard and System Performance Optimization
    Web Interface & Telemetry:
    - Integrated real-time Battery Voltage and Current monitoring into the dashboard.
    - Added side-by-side progress bars for Battery Percentage and Current for better visual feedback.
    - Implemented high-precision decimal readouts for Measured Voltage and Current in the dashboard footer.
    - Added raw sensor voltage monitoring from IMON_PIN (Current Sensor) to aid in hardware diagnostics and calibration.
    - Optimized the '/data' JSON endpoint:
2026-05-31 project aligned: storage and telemetry fixed for all buoys
2026-06-03 feat(sub): refactor web dashboard to serve from LittleFS
    This commit transitions the Sub unit's web dashboard from a hardcoded
    string in the firmware to a standalone file served from the ESP32's
    internal filesystem (LittleFS).
    Key Changes:
    - **Project Structure**: Extracted the embedded HTML/CSS/JS from src/subwifi.cpp
    into a new data/index.html file, aligning with the RoboTop project's
2026-06-03 fix: restore baseline filter for rudder PID
2026-06-03 fix: Robust message bridging, optimized telemetry, and fixed setup data corruption
    Core Updates:
    - Implemented 'Smart Bridging' in RoboTop to seamlessly route messages between LoRa and UDP without redundant echos.
    - Optimized RoboDependency library to skip empty data fields in GET/ACK packets, significantly reducing network overhead.
    - Fixed RoboTop data corruption issue where uninitialized structs were being broadcast during setup requests.
    - Added immediate cache-based responses for SETUPDATA in RoboTop for faster UI feedback.
    Monitor & UI:
2026-06-03 feat: Major Version 4.0.0 - Comprehensive Protocol & Dashboard Refactor
    This major release overhauls the communication architecture and diagnostic capabilities of the RoboBuoy system.
    Key Changes:
    - Dashboard: Implemented Quad-Window telemetry (UDP/LoRa IN/OUT) and 1400px wide UI.
    - Protocol: Shifted to strict LORAINF (ACK=6) validation to ensure data consistency.
    - Bridging: Rewrote RoboTop relay logic to eliminate network echos and bridge interfaces efficiently.
    - Optimization: RoboDependency now truncates empty fields in GET/ACK packets for low bandwidth.
2026-06-03 fix: Reduce rudder overshoot by increasing heading filter alpha and restoring anti-windup logic
2026-06-04 feat(ui): update dashboard with wind telemetry and enhanced status visibility
    - Added Wind and STD telemetry display in top-right corner.
    - Restricted Wind/STD and Target/Distance visibility based on buoy mode (LOCKED/IDLE).
    - Standardized current scale to -5A to +20A and embedded values in progress bars.
    - Restored PID I-term displays below motor bars.
    - Streamlined setup popup by removing in-water calibration and aligning buttons.
2026-06-04 fix(comm): improve setup data synchronization and robust buoy identification
    - Implement 'Collecting data...' overlay in Top web interface with a 5-second timeout.
    - Disable message truncation optimization in RoboCompute to ensure full parameter transfer.
    - Update RoboSub to respond with LORAINF for SETUPDATA requests to avoid truncation.
    - Refactor Top buoy data routing to prioritize local serial data for the Main slot.
    - Implement ID synchronization between Top and Sub controllers.
    - Improve RoboControl.py with better buoy frame identification and packet handling.
2026-06-04 feat(ui): add thruster inversion and swap settings to setup popup
    - Implemented UI controls for BB/SB inversion and thruster swap in index.html.
    - Added backend support in topwifi.cpp to serve and update these settings via /data and /command endpoints.
    - Synchronized RoboControl.py with the updated data structure.
2026-06-05 Complete protocol synchronization and Web UI updates for holdRad
    Detailed changes:
    - Web Interface:
    * Added 'Radius' (holdRad) input field to the Setup modal.
    * Implemented revision-based data fetching: The UI now waits for a NEW data
    revision from the Sub before showing the Setup modal, ensuring data is never stale.
    * Added safety check to prevent saving zeroed-out critical PID/Speed values.
2026-06-05 Update RoboControl.py to support v4.0 protocol with holdRad
2026-06-09 feat(sub): implement compass watchdog and optimize web dashboard low-latency performance
    - Compass Watchdog: Added a stuck-heading watchdog in src/compass.cpp. If the heading remains completely static for over 5 minutes, it displays 'COMPASS STUCK - REINIT' and calls InitCompass() to aut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
    - Web Dashboard Keep-Alive: Removed the anti-cache query parameter from '/data' fetches in data/index.html and src/index_html.h, aligning with RoboTop. This enables HTTP Keep-Alive and prevents LwIP 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
    - Smooth 60 FPS Windrose: Implemented a requestAnimationFrame-driven easing loop (interpolating 15% per frame with shortest-path circular wrap-around)
2026-06-11 feat(web): add real-time horizontal battery voltage bar below the windrose
    - UI Design: Stacked a horizontal battery voltage container directly below the circular windrose canvas, centered to match the panel layout.
    - Dimensional Consistency: Made the voltage bar thickness (30px) and width (400px) match the side panels and canvas dimensions for absolute layout balance.
    - Range & Color Coding: Configured the bar scale from 17.0V to 26.0V. Set dynamic color-coding logic: Green for >=22.0V, Yellow for 19.0V to 22.0V, and Red for <19.0V.
    - Precision Labeling: Plotted the actual voltage in the middle of the bar with one-decimal-place precision (one digit precision).
    - Telemetry Integration: Added
2026-06-13 docs(firmware): add extensive inline comments explaining architecture, protocols, and safety mechanisms
    - Added detailed explanations to `formatFloat()` and `RoboDecode()` inside `RoboCompute.cpp` covering bandwidth optimization and RF packet decoding.
    - Documented LoRa task queues, polling buffers, retries, and hardware transceiver self-healing procedures in `LiLlora.cpp` and `loratop.cpp`.
    - Added clear documentation inside `sercom.cpp` explaining half-duplex single-wire line echo prevention and implicit ACK protocols.
    - Added comprehensive comments in `main.cpp` (RoboTop) detailing asynchronous setup forwarding mechanisms and persistent EEPROM configuration storage.
    - Documented Python co
2026-06-13 docs: promote comprehensive master README.md to repository root
    - Copied the highly detailed master README.md from Firmware/ to the repository root directory.
    - This ensures that GitHub correctly displays the full system description, architecture diagrams, protocol frames, and developer guidelines on the repository home page.
2026-06-17 docs(firmware): add dedicated README files for RoboTop, RoboLora, RoboDependency, and RoboPythonDisplay
2026-06-25 feat(firmware): resolve ESC transition hiccup and fix idle power bar telemetry
    - Fixed the ESC 'hiccup' when transitioning from the blending transition stage to the normal stage in Locked Mode.
    - Promoted was_pure_pivot to the file-level scope in src/pidrudspeed.cpp to coordinate state between speed and rudder state machines.
    - Modified the locked mode state machine to perform speed and rudder PID resets only once on entry to pure pivot, eliminating continuous resets.
    - Implemented 'conditional integration' in speedPid by pausing Speed PID calculations and holding target speed at 0 while in pure pivot mode. This prevents integral windup during the pivot phase, all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
